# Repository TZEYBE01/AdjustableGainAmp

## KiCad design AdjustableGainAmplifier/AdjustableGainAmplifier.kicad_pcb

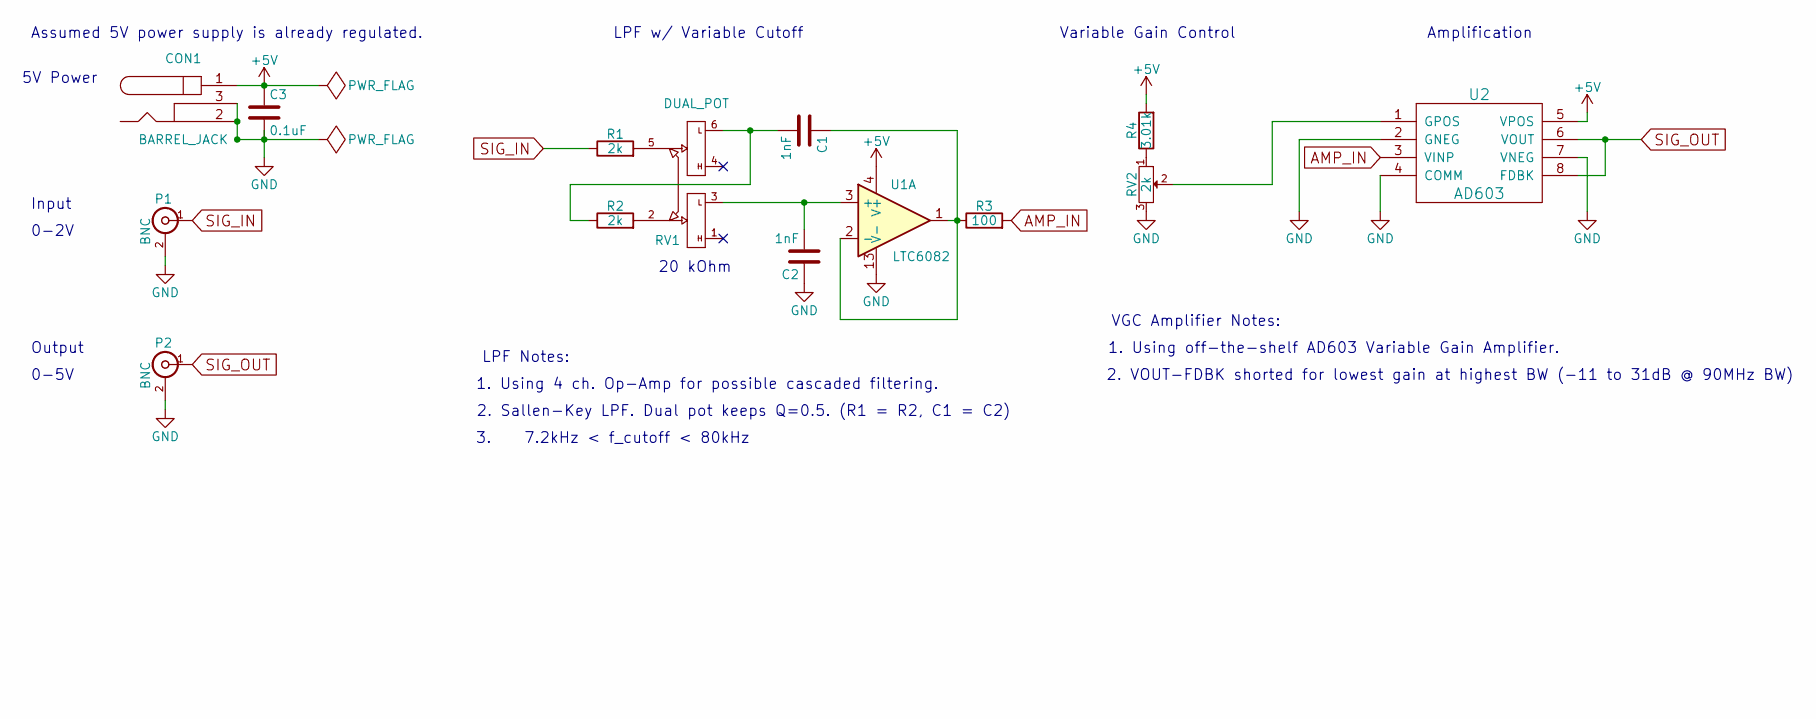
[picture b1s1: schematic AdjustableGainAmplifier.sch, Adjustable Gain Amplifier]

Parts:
C1, C2: 1nF; C_1206_HandSoldering
C3: 0.1uF; C_1206_HandSoldering
CON1: BARREL_JACK
P1, P2: BNC; BNC_Socket_TYCO-AMP
R1, R2: 2k; R_1206_HandSoldering
R3: 100; R_1206_HandSoldering
R4: 3.01k; R_1206_HandSoldering
RV1: DUAL_POT; 20k_DualPot
RV2: 2k; 2k_POT_SMD
U1: LTC6082; SSOP-16_3.9x4.9mm_Pitch0.635mm
U2: AD603; SOIC-8_3.9x4.9mm_Pitch1.27mm

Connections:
+5V: C3.1, CON1.1, R4.2, U1.4 (V+), U2.5 (VPOS)
AMP_IN: R3.2, U2.3 (VINP)
GND: C2.1, C3.2, CON1.2, CON1.3, P1.2 (Ext), P2.2 (Ext), RV2.3, U1.13 (V-), U2.2 (GNEG), U2.4 (COMM), U2.7 (VNEG)
unnamed: C1.1, R3.1, U1.1, U1.2 (-)
unnamed: C1.2, R2.1, RV1.6
unnamed: C2.2, RV1.3, U1.3 (+)
unnamed: R1.2, RV1.5
unnamed: R2.2, RV1.2
unnamed: R4.1, RV2.1
unnamed: RV2.2, U2.1 (GPOS)
SIG_IN: P1.1 (In), R1.1
SIG_OUT: P2.1 (In), U2.6 (VOUT), U2.8 (FDBK)

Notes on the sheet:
Assumed 5V power supply is already regulated.
Input
0-2V
5V Power
Variable Gain Control
Amplification
Output
0-5V
LPF w/ Variable Cutoff
LPF Notes:
1. Using 4 ch. Op-Amp for possible cascaded filtering.
2. Sallen-Key LPF. Dual pot keeps Q=0.5. (R1 = R2, C1 = C2)
3. 7.2kHz < f_cutoff < 80kHz
VGC Amplifier Notes:
1. Using off-the-shelf AD603 Variable Gain Amplifier.
2. VOUT-FDBK shorted for lowest gain at highest BW (-11 to 31dB @ 90MHz BW)
20 kOhm

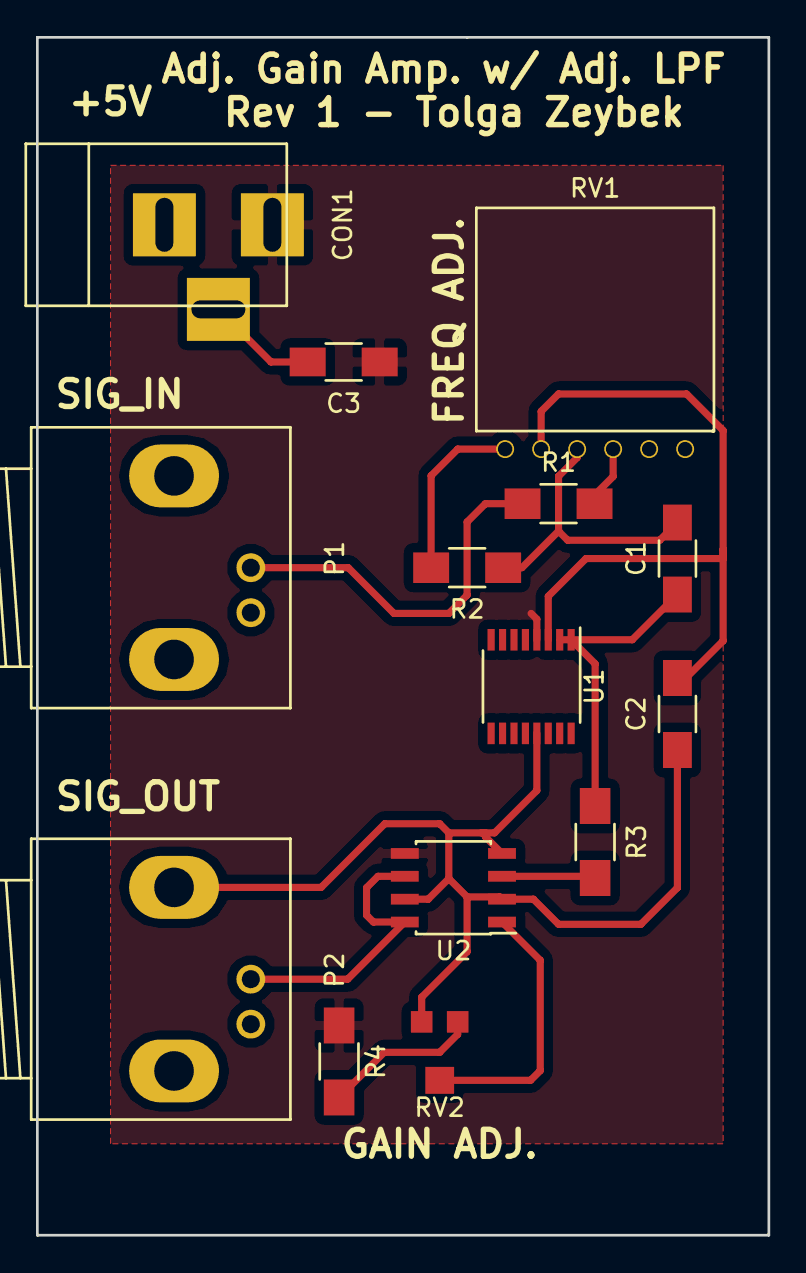
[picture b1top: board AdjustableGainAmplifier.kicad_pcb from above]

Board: 2 copper layers, 40.6 x 66.5 mm, 14 parts (0 on the bottom side), 12 nets.

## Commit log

2016-12-12 :lollipop: Added .gitattributes & .gitignore files
2016-12-12 Adding all files
2016-12-12 Relocation of docs
